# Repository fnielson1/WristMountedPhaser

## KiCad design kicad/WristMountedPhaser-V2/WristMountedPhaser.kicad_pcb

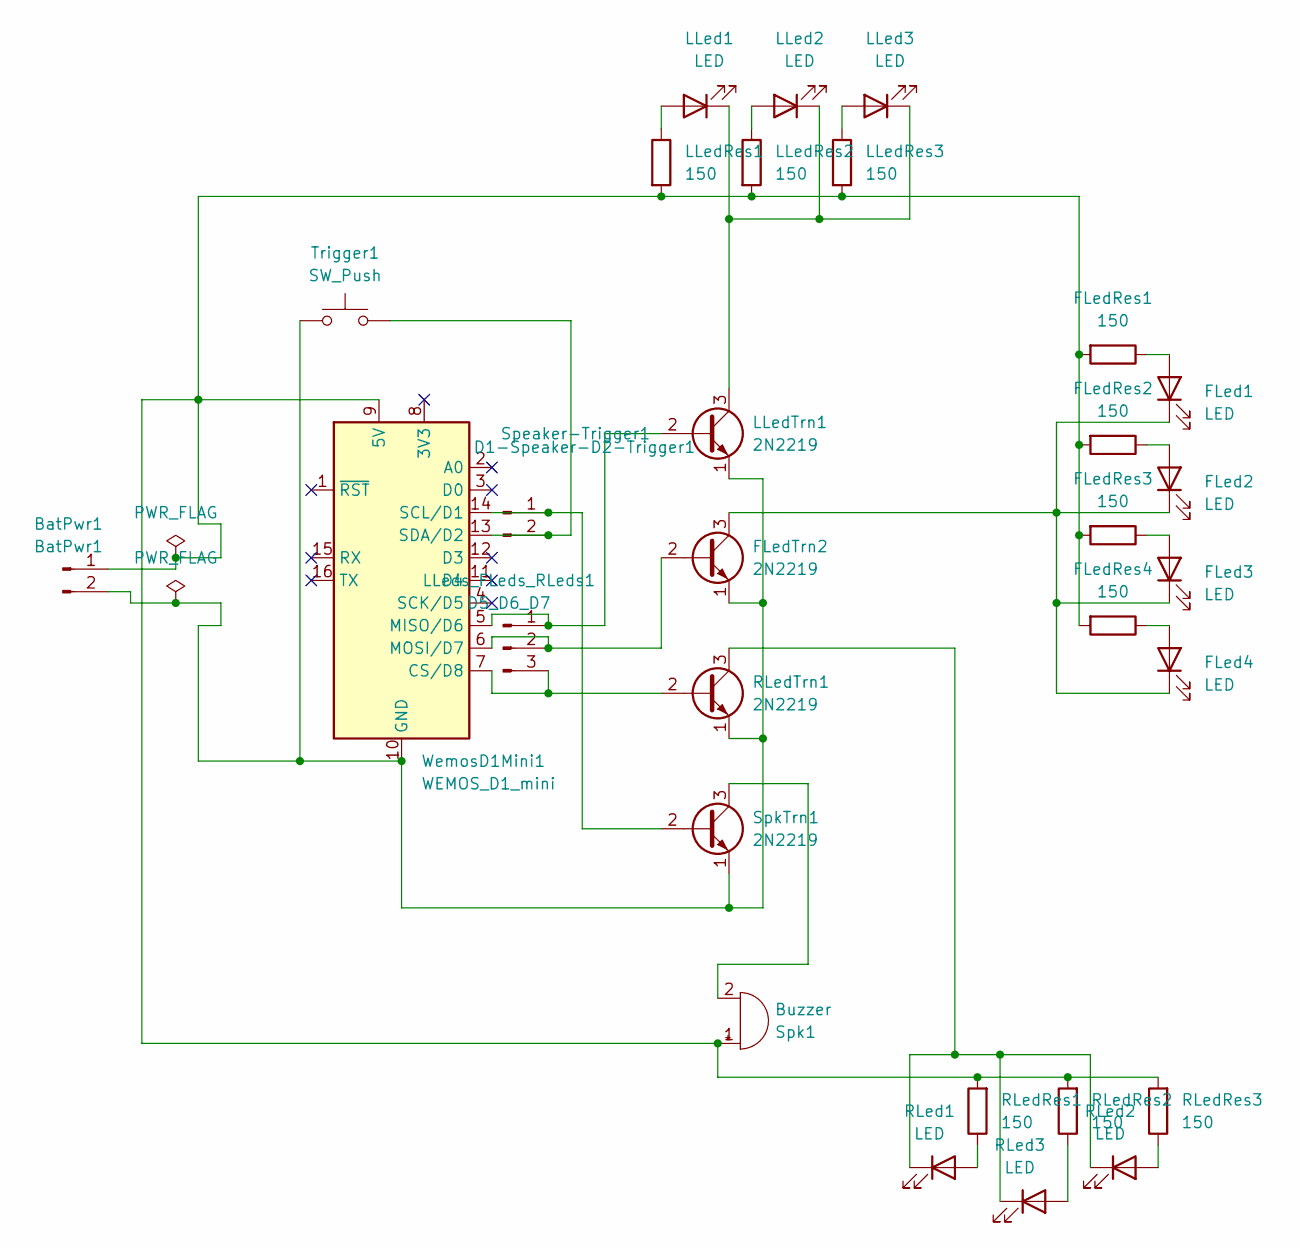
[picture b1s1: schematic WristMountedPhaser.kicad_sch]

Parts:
BatPwr1: BatPwr1; PinHeader_1x02_P2.54mm_Vertical
FLed1, FLed2, FLed3, FLed4: LED; PinHeader_1x02_P2.54mm_Vertical
FLedRes1, FLedRes2, FLedRes3, FLedRes4: 150; R_Axial_DIN0207_L6.3mm_D2.5mm_P7.62mm_Horizontal
FLedTrn2: 2N2219; TO-92_Inline_BJT
LLed1, LLed2, LLed3: LED; PinHeader_1x02_P2.54mm_Vertical
LLedRes1, LLedRes2, LLedRes3: 150; R_Axial_DIN0207_L6.3mm_D2.5mm_P7.62mm_Horizontal
LLedTrn1: 2N2219; TO-92_Inline_BJT
LLeds_FLeds_RLeds1: D5_D6_D7; PinHeader_1x03_P2.54mm_Vertical
RLed1, RLed2, RLed3: LED; PinHeader_1x02_P2.54mm_Vertical
RLedRes1, RLedRes2, RLedRes3: 150; R_Axial_DIN0207_L6.3mm_D2.5mm_P7.62mm_Horizontal
RLedTrn1: 2N2219; TO-92_Inline_BJT
Speaker-Trigger1: D1-Speaker-D2-Trigger1; PinHeader_1x02_P2.54mm_Vertical
Spk1: Buzzer; PinHeader_1x02_P2.54mm_Vertical
SpkTrn1: 2N2219; TO-92_Inline_BJT
Trigger1: SW_Push; PinHeader_1x02_P2.54mm_Vertical
WemosD1Mini1: WEMOS_D1_mini; WEMOS_D1_mini_light

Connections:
unnamed 0: BatPwr1.1, FLedRes1.2, FLedRes2.2, FLedRes3.2, FLedRes4.2, LLedRes1.2, LLedRes2.2, LLedRes3.2, RLedRes1.2, RLedRes2.2, RLedRes3.2, Spk1.1 (+), WemosD1Mini1.9 (5V); also elsewhere on the board
unnamed 1: BatPwr1.2, FLedTrn2.1 (E), LLedTrn1.1 (E), RLedTrn1.1 (E), SpkTrn1.1 (E), Trigger1.1, WemosD1Mini1.10 (GND); also elsewhere on the board
unnamed: FLed1.2 (A), FLedRes1.1
unnamed: FLed1.1 (K), FLed2.1 (K), FLed3.1 (K), FLed4.1 (K), FLedTrn2.3 (C)
unnamed: FLed2.2 (A), FLedRes2.1
unnamed: FLed3.2 (A), FLedRes3.1
unnamed: FLed4.2 (A), FLedRes4.1
unnamed: FLedTrn2.2 (B), LLeds_FLeds_RLeds1.2, WemosD1Mini1.6 (MOSI/D7)
unnamed: LLed1.2 (A), LLedRes1.1
unnamed: LLed1.1 (K), LLed2.1 (K), LLed3.1 (K), LLedTrn1.3 (C)
unnamed: LLed2.2 (A), LLedRes2.1
unnamed: LLed3.2 (A), LLedRes3.1
unnamed: LLedTrn1.2 (B), LLeds_FLeds_RLeds1.1, WemosD1Mini1.5 (MISO/D6)
unnamed: LLeds_FLeds_RLeds1.3, RLedTrn1.2 (B), WemosD1Mini1.7 (CS/D8)
unnamed: RLed1.2 (A), RLedRes1.1
unnamed: RLed1.1 (K), RLed2.1 (K), RLed3.1 (K), RLedTrn1.3 (C)
unnamed: RLed2.2 (A), RLedRes3.1
unnamed: RLed3.2 (A), RLedRes2.1
unnamed: Speaker-Trigger1.1, SpkTrn1.2 (B), WemosD1Mini1.14 (SCL/D1)
unnamed: Speaker-Trigger1.2, Trigger1.2, WemosD1Mini1.13 (SDA/D2)
unnamed: Spk1.2 (-), SpkTrn1.3 (C)

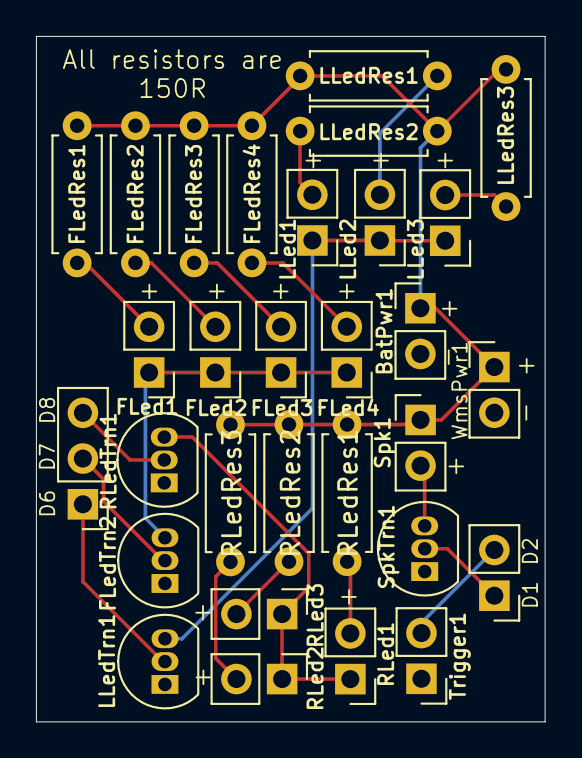
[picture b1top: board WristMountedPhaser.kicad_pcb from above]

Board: 2 copper layers, 28.3 x 38.1 mm, 30 parts (0 on the bottom side), 21 nets.

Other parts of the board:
WmsPwr1: BatPwr1; PinHeader_1x02_P2.54mm_Vertical

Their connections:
unnamed 0: WmsPwr1.1; also elsewhere on the board
unnamed 1: WmsPwr1.2; also elsewhere on the board

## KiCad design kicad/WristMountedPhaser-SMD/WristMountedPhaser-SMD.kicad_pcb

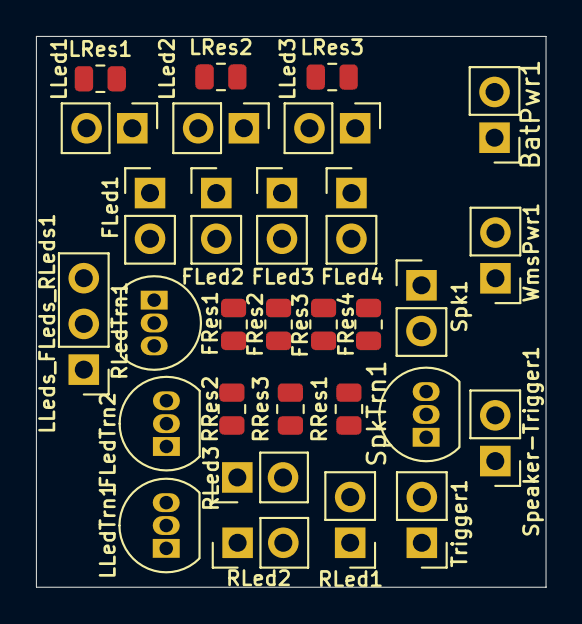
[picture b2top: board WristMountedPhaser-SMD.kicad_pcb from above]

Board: 2 copper layers, 28.3 x 30.6 mm, 30 parts (0 on the bottom side), 21 nets, no tracks yet.

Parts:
BatPwr1: BatPwr; PinHeader_1x02_P2.54mm_Vertical
FLed1, FLed2, FLed3, FLed4: LED; PinHeader_1x02_P2.54mm_Vertical
FLedTrn2: SS8050; TO-92_Inline_BJT
FRes1, FRes2, FRes3, FRes4: 150; R_0805_2012Metric
LLed1, LLed2, LLed3: LED; PinHeader_1x02_P2.54mm_Vertical
LLedTrn1: SS8050; TO-92_Inline_BJT
LLeds_FLeds_RLeds1: D5_D6_D7; PinHeader_1x03_P2.54mm_Vertical
LRes1, LRes2, LRes3: 150; R_0805_2012Metric
RLed1, RLed2, RLed3: LED; PinHeader_1x02_P2.54mm_Vertical
RLedTrn1: SS8050; TO-92_Inline_BJT
RRes1, RRes2, RRes3: 150; R_0805_2012Metric
Speaker-Trigger1: D1-Speaker-D2-Trigger1; PinHeader_1x02_P2.54mm_Vertical
Spk1: Buzzer; PinHeader_1x02_P2.54mm_Vertical
SpkTrn1: SS8050; TO-92_Inline_BJT
Trigger1: SW_Push; PinHeader_1x02_P2.54mm_Vertical
WmsPwr1: WemosPower1; PinHeader_1x02_P2.54mm_Vertical

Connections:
unnamed: BatPwr1.1, FRes1.2, FRes2.2, FRes3.2, FRes4.2, LRes1.2, LRes2.2, LRes3.2, RRes1.2, RRes2.2, RRes3.2, Spk1.1 (+), WmsPwr1.2
unnamed: BatPwr1.2, FLedTrn2.2 (E), LLedTrn1.2 (E), RLedTrn1.2 (E), SpkTrn1.2 (E), Trigger1.1, WmsPwr1.1
unnamed: FLed1.2 (A), FRes1.1
unnamed: FLed1.1 (K), FLed2.1 (K), FLed3.1 (K), FLed4.1 (K), FLedTrn2.3 (C)
unnamed: FLed2.2 (A), FRes2.1
unnamed: FLed3.2 (A), FRes3.1
unnamed: FLed4.2 (A), FRes4.1
unnamed: FLedTrn2.1 (B), LLeds_FLeds_RLeds1.2
unnamed: LLed1.2 (A), LRes1.1
unnamed: LLed1.1 (K), LLed2.1 (K), LLed3.1 (K), LLedTrn1.3 (C)
unnamed: LLed2.2 (A), LRes2.1
unnamed: LLed3.2 (A), LRes3.1
unnamed: LLedTrn1.1 (B), LLeds_FLeds_RLeds1.1
unnamed: LLeds_FLeds_RLeds1.3, RLedTrn1.1 (B)
unnamed: RLed1.2 (A), RRes1.1
unnamed: RLed1.1 (K), RLed2.1 (K), RLed3.1 (K), RLedTrn1.3 (C)
unnamed: RLed2.2 (A), RRes3.1
unnamed: RLed3.2 (A), RRes2.1
unnamed: Speaker-Trigger1.1, SpkTrn1.1 (B)
unnamed: Speaker-Trigger1.2, Trigger1.2
unnamed: Spk1.2 (-), SpkTrn1.3 (C)
